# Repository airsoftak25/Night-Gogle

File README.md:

# Night-Gogle
My small project about creating a Night vision gogle witch cost less than 2000CZK each

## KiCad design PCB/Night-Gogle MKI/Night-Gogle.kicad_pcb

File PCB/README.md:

# Description
This folder contains all KiCad project, libfiles and DWG files

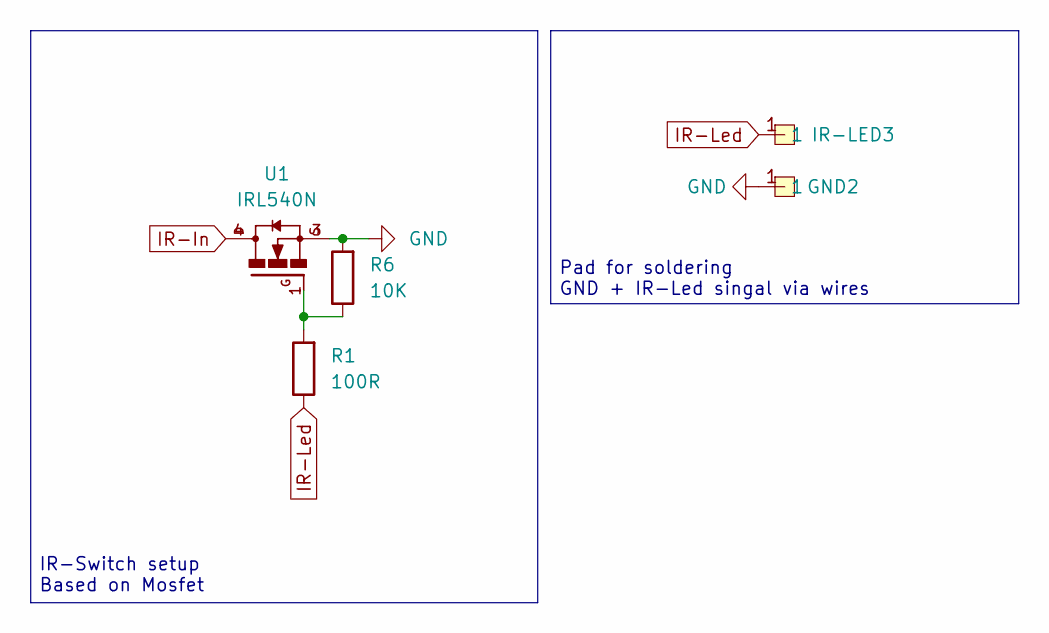
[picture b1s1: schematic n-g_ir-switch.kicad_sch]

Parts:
GND2: Pad-3.5mm
IR-LED3: Pad-3.5mm
R1: 100R; R_0805_2012Metric_Pad1.20x1.40mm_HandSolder
R6: 10K; R_0805_2012Metric_Pad1.20x1.40mm_HandSolder
U1: IRL540N; TO254P1524X483-4N

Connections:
GND: GND2.1, R6.2, U1.3; also elsewhere on the board
IR-In: U1.4; also elsewhere on the board
IR-Led: IR-LED3.1, R1.1; also elsewhere on the board
unnamed: R1.2, R6.1, U1.1

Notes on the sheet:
Pad for soldering GND + IR-Led singal via wires
IR-Switch setup Based on Mosfet

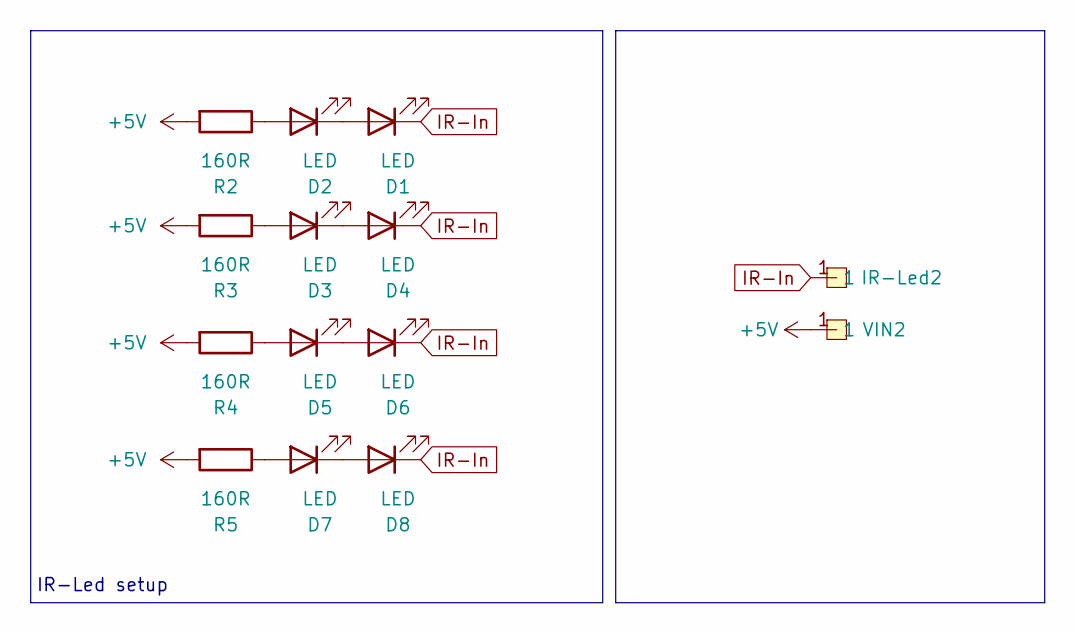
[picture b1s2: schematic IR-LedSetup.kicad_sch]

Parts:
D1, D2, D3, D4, D5, D6, D7, D8: LED; LED_D5.0mm
IR-Led2: Pad-3.5mm
R2, R3, R4, R5: 160R; R_1206_3216Metric_Pad1.30x1.75mm_HandSolder
VIN2: Pad-3.5mm

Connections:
+5V: R2.2, R3.2, R4.2, R5.2, VIN2.1; also elsewhere on the board
IR-In: D1.1 (K), D4.1 (K), D6.1 (K), D8.1 (K), IR-Led2.1; also elsewhere on the board
unnamed: D1.2 (A), D2.1 (K)
unnamed: D2.2 (A), R2.1
unnamed: D3.2 (A), R3.1
unnamed: D3.1 (K), D4.2 (A)
unnamed: D5.2 (A), R4.1
unnamed: D5.1 (K), D6.2 (A)
unnamed: D7.2 (A), R5.1
unnamed: D7.1 (K), D8.2 (A)

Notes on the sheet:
IR-Led setup

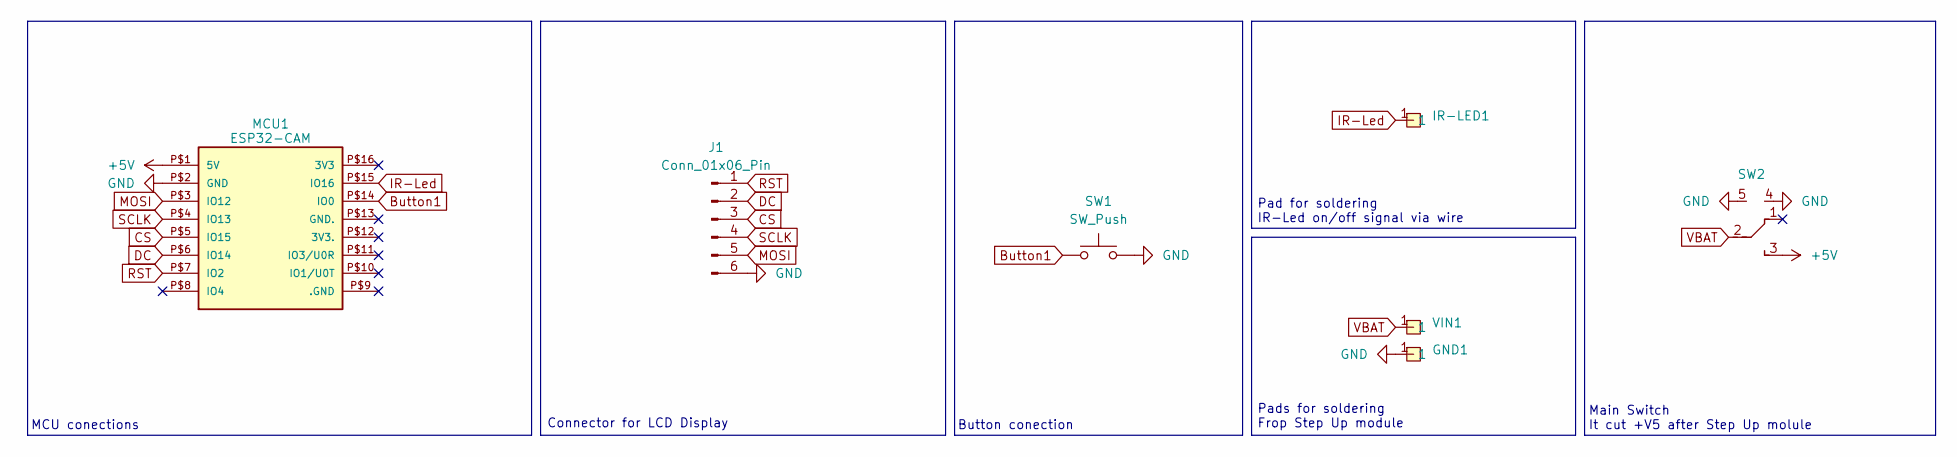
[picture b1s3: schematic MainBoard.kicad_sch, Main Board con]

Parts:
GND1: Pad-3.5mm
IR-LED1: Pad-3.5mm
J1: Conn_01x06_Pin; JST_SH_SM06B-SRSS-TB_1x06-1MP_P1.00mm_Horizontal
MCU1: ESP32-CAM
SW1: SW_Push; TD-03X
SW2: 255SB (B1408) - Vertical
VIN1: Pad-3.5mm

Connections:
+5V: MCU1.P$1 (5V), SW2.3; also elsewhere on the board
Button1: MCU1.P$14 (IO0), SW1.1
CS: J1.3, MCU1.P$5 (IO15)
DC: J1.2, MCU1.P$6 (IO14)
GND: GND1.1, J1.6, MCU1.P$2 (GND), MCU1.P$9 (.GND), MCU1.P$13 (GND.), SW1.2, SW2.4, SW2.5; also elsewhere on the board
IR-Led: IR-LED1.1, MCU1.P$15 (IO16); also elsewhere on the board
MOSI: J1.5, MCU1.P$3 (IO12)
RST: J1.1, MCU1.P$7 (IO2)
SCLK: J1.4, MCU1.P$4 (IO13)
VBAT: SW2.2, VIN1.1

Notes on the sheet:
MCU conections
Button conection
Pads for soldering Frop Step Up module
Connector for LCD Display
Pad for soldering IR-Led on/off signal via wire
Main Switch It cut +V5 after Step Up molule

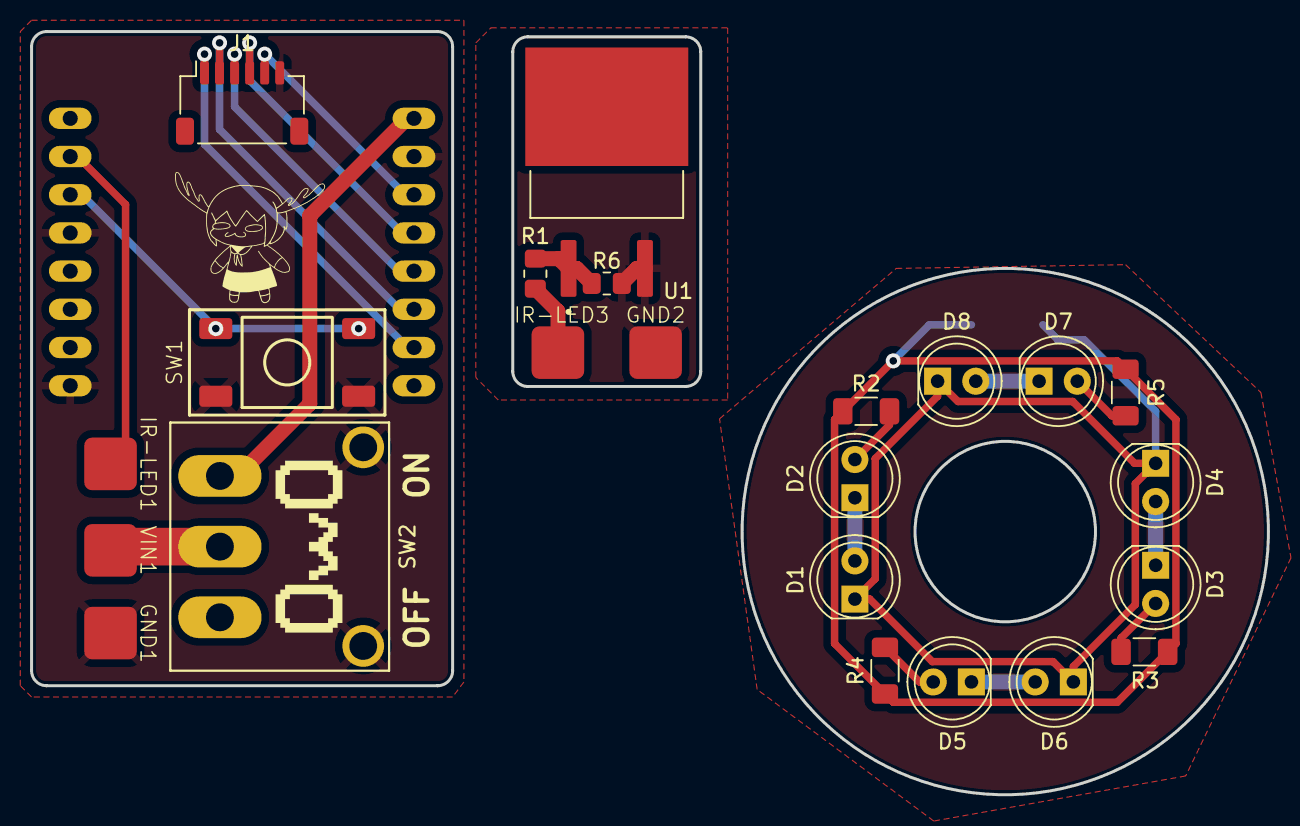
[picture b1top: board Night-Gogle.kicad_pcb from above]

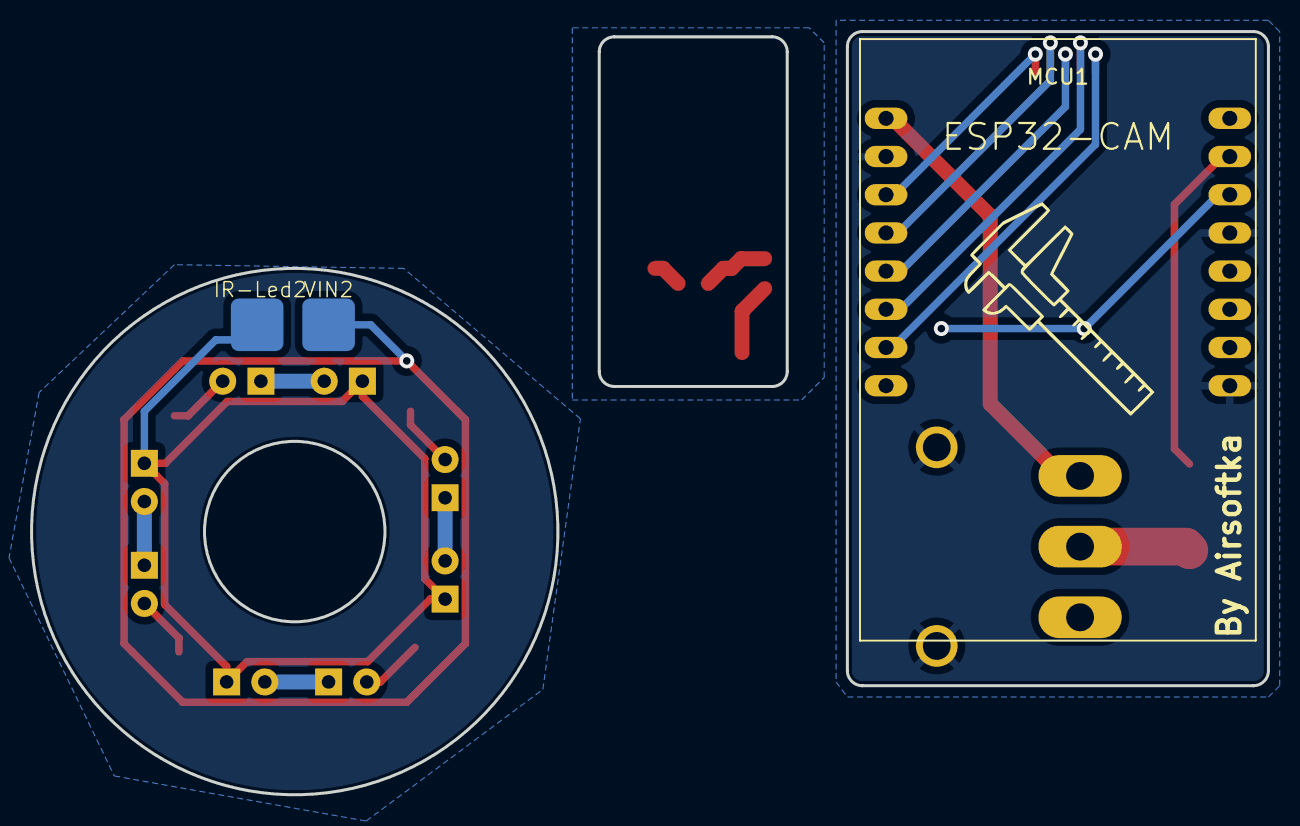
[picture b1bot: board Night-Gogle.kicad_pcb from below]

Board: 2 copper layers, 82.2 x 50.8 mm, 26 parts (3 on the bottom side), 20 nets.

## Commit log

2025-05-26 Update README files and add XXlX file
2025-05-29 CODE
    lol
2025-05-30 pcb update
    was created main board pcb + pice of IR_led
2025-06-01 pcb update
2025-06-19 Big Update
2025-06-20 3d update
2025-07-15 model rework
